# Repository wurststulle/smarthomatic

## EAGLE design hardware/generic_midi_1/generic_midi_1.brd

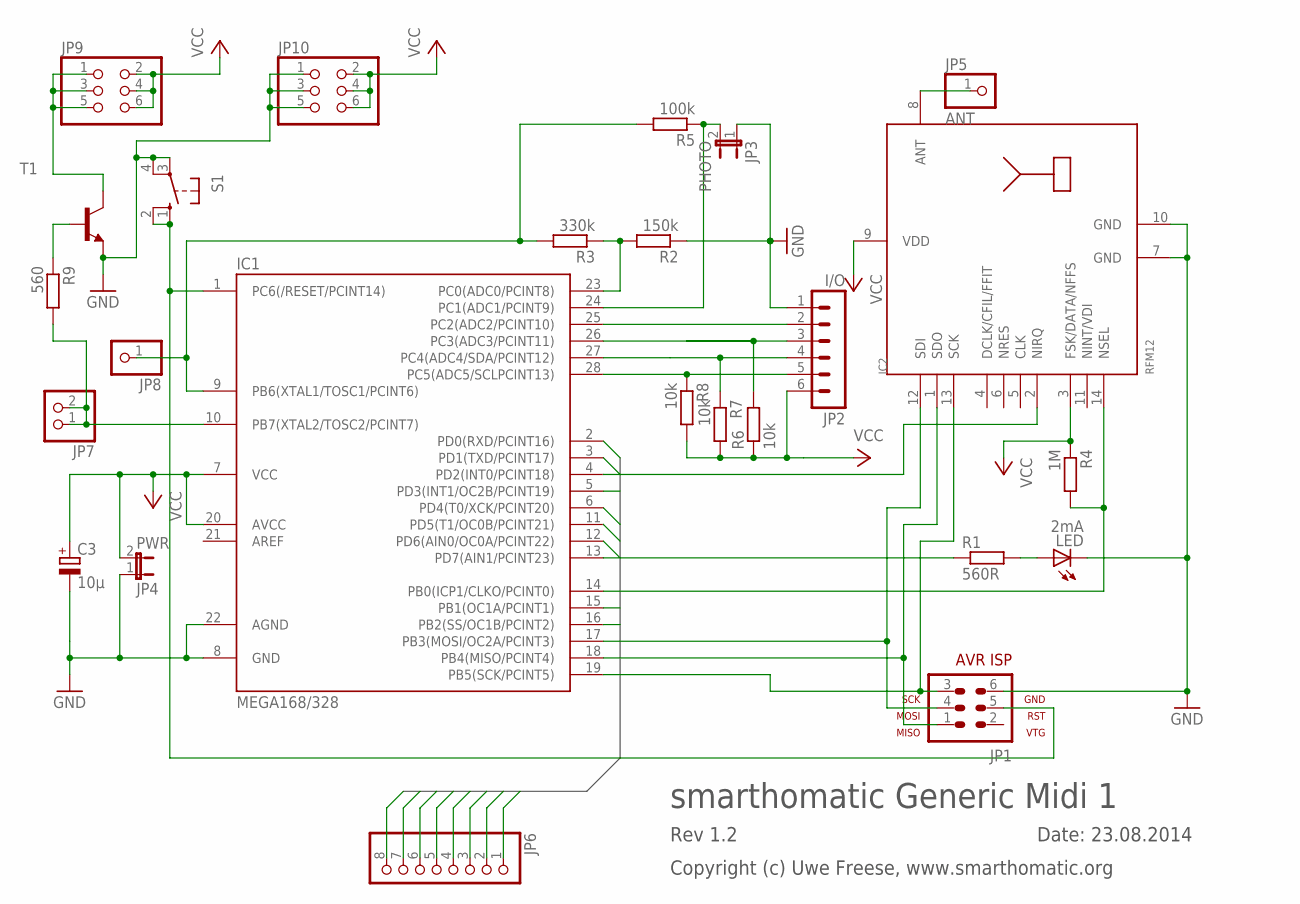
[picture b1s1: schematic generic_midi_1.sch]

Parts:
C3: 10µ; E1,8-4
IC1: MEGA168/328; DIL28-3
IC2: RFM12; RFM
JP1: AVR-ISP-6
JP2: I/O; MA06-1
JP3: PHOTO; JP1
JP4: PWR; JP1
JP5: ANT; 1X01
JP6: PINHD-1X8; 1X08
JP7: PINHD-1X2; 1X02
JP8: PINHD-1X1; 1X01
JP9, JP10: PINHD-2X3; 2X03
LED: 2mA; LED3MM
R1: 560R; 0207/7
R2: 150k; 0207/7
R3: 330k; 0207/7
R4: 1M; 0207/7
R5: 100k; 0207/7
R6, R7, R8: 10k; 0207/7
R9: 560; 0207/7
S1: 10-XX; B3F-10XX
T1: BC547-NPN-TO92-CBE; TO92-CBE

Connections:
GND: C3.-, IC1.8 (GND), IC1.22 (AGND), IC2.7 (GND), IC2.10 (GND), JP1.6, JP2.1, JP3.1, JP4.1, JP10.1, JP10.3, JP10.5, LED.K (C), R2.1, S1.3, S1.4 (P1), T1.E
IO0: IC1.3 (PD1(TXD/PCINT17)), JP6.1
IO1: IC1.2 (PD0(RXD/PCINT16)), JP6.2
IO2: IC1.5 (PD3(INT1/OC2B/PCINT19)), JP6.3
IO3: IC1.6 (PD4(T0/XCK/PCINT20)), JP6.4
IO4: IC1.11 (PD5(T1/OC0B/PCINT21)), JP6.5
IO5: IC1.12 (PD6(AIN0/OC0A/PCINT22)), JP6.6
IO6: IC1.15 (PB1(OC1A/PCINT1)), JP6.7
IO7: IC1.16 (PB2(SS/OC1B/PCINT2)), JP6.8
unnamed: IC1.24 (PC1(ADC1/PCINT9)), JP3.2, R5.1
unnamed: IC1.17 (PB3(MOSI/OC2A/PCINT3)), IC2.12 (SDI), JP1.4
unnamed: IC1.18 (PB4(MISO/PCINT4)), IC2.1 (SDO), JP1.1
unnamed: IC1.19 (PB5(SCK/PCINT5)), IC2.13 (SCK), JP1.3
unnamed: IC1.13 (PD7(AIN1/PCINT23)), R1.1
unnamed: IC1.27 (PC4(ADC4/SDA/PCINT12)), JP2.4, R7.1
unnamed: IC1.1 (PC6(/RESET/PCINT14)), JP1.5, S1.1 (S), S1.2 (S1)
unnamed: IC1.28 (PC5(ADC5/SCLPCINT13)), JP2.5, R8.1
unnamed: IC1.26 (PC3(ADC3/PCINT11)), JP2.3, R6.2
unnamed: IC2.8 (ANT), JP5.1
unnamed: LED.A, R1.2
unnamed: IC1.14 (PB0(ICP1/CLKO/PCINT0)), IC2.14 (NSEL), R4.2
unnamed: IC1.10 (PB7(XTAL2/TOSC2/PCINT7)), JP7.1, JP7.2, R9.2
unnamed: IC1.4 (PD2(INT0/PCINT18)), IC2.2 (NIRQ)
unnamed: JP9.1, JP9.3, JP9.5, T1.C
unnamed: R9.1, T1.B
unnamed: IC1.23 (PC0(ADC0/PCINT8)), R2.2, R3.1
unnamed: IC1.25 (PC2(ADC2/PCINT10)), JP2.2
unnamed: IC1.9 (PB6(XTAL1/TOSC1/PCINT6)), JP8.1, R3.2, R5.2
VCC: C3.+, IC1.7 (VCC), IC1.20 (AVCC), IC2.3 (FSK/DATA/NFFS), IC2.9 (VDD), JP2.6, JP4.2, JP9.2, JP9.4, JP9.6, JP10.2, JP10.4, JP10.6, R4.1, R6.1, R7.2, R8.2

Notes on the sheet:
smarthomatic Generic Midi 1
Date: 23.08.2014
Rev 1.2
Copyright (c) Uwe Freese, www.smarthomatic.org

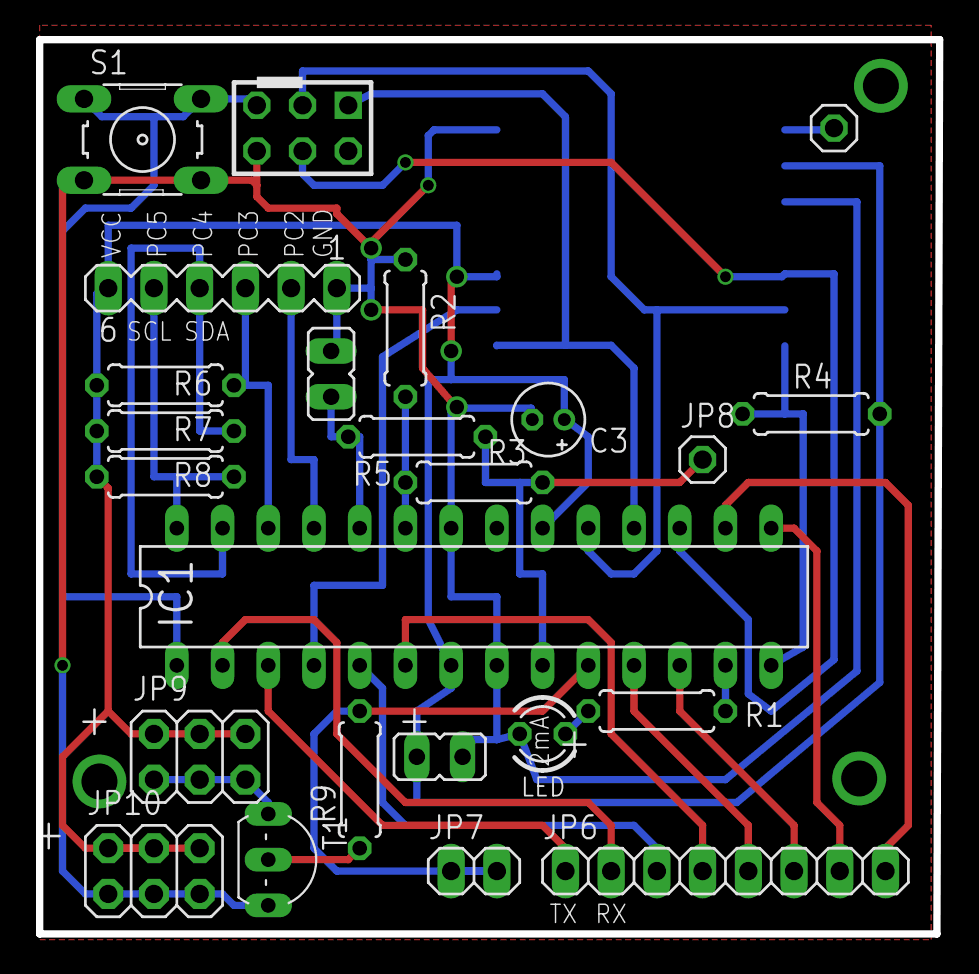
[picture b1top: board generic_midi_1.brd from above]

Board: 2 copper layers, 50.0 x 49.7 mm, 25 parts (1 on the bottom side), 29 nets.

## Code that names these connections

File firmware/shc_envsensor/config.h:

/*
* This file is part of smarthomatic, http://www.smarthomatic.org.
* Copyright (c) 2013 Uwe Freese
*
* smarthomatic is free software: you can redistribute it and/or modify it
* under the terms of the GNU General Public License as published by the
* Free Software Foundation, either version 3 of the License, or (at your
* option) any later version.
*
* smarthomatic is distributed in the hope that it will be useful, but
* WITHOUT ANY WARRANTY; without even the implied warranty of
* MERCHANTABILITY or FITNESS FOR A PARTICULAR PURPOSE. See the GNU General
* Public License for more details.
*
* You should have received a copy of the GNU General Public License along
* with smarthomatic. If not, see <http://www.gnu.org/licenses/>.
*/

#include <stdint.h>
#include <avr/io.h>
#include <util/delay.h>

// SHT11 hum/temp sensor

#define SHT11_AT_5V         4010
#define SHT11_AT_4V         3980
#define SHT11_AT_3_5V       3970
#define SHT11_AT_3V         3960
#define SHT11_AT_2_5V       3940

#define SHT11_TEMP_V_COMP   SHT11_AT_3V

#define SHT11_RES_LOW       1  //8_12_Bit
#define SHT11_RES_HIGH      0  //12_14_Bit
#define SHT11_RESOLUTION    SHT11_RES_HIGH

#define SHT11_PORT	        C
#define SHT11_SCL	        (1<<PC2) // was: PC4!
#define SHT11_SDA	        (1<<PC3)
#define SHT11_LOWRES	    SHT11_RESOLUTION	

// DHT11 hum/temp sensor

#define DHT_DDR DDRB
#define DHT_PORT PORTB
#define DHT_PIN PINB
#define DHT_INPUTPIN PB1

// ---

#define GLUE(a, b)	a##b
#define PORT(x)		GLUE(PORT, x)
#define PIN(x)		GLUE(PIN, x)
#define DDR(x)		GLUE(DDR, x)

#define setBits(port,mask)	do{ (port) |=  (mask); }while(0)
#define clrBits(port,mask)	do{ (port) &= ~(mask); }while(0)
#define tstBits(port,mask)	((port) & (mask))

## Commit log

2014-08-23 do countWakeup only when value is set
2014-08-23 send all values that ready, not only the first one
2014-08-24 add support for DHT11
2014-09-01 change dht11 pin
2014-09-02 test
2014-09-15 fix transistor
2015-02-20 rgb_dimmer: add gpio functions
2015-02-24 rgb dimmer: - add setgetsave message type - save default color and brightness
2015-02-24 rgb dimmer: - change loading of default color after startup
2015-02-24 rgb dimmer + gpio: fix e2p layout for switches
2015-02-25 rgb dimmer + gpio: fix for message group processing
